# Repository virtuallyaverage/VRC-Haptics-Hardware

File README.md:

# Development moved to: https://github.com/VRC-Haptics/VRCH-Hardware

Hardware implementation for vrc haptics project. See: Firmware: [VRC-Haptics-Firmware](https://github.com/virtuallyaverage/VRC-Haptics-Firmware), Server: [VRC-Haptics-Hardware](https://github.com/virtuallyaverage/VRC-Haptics-Host)

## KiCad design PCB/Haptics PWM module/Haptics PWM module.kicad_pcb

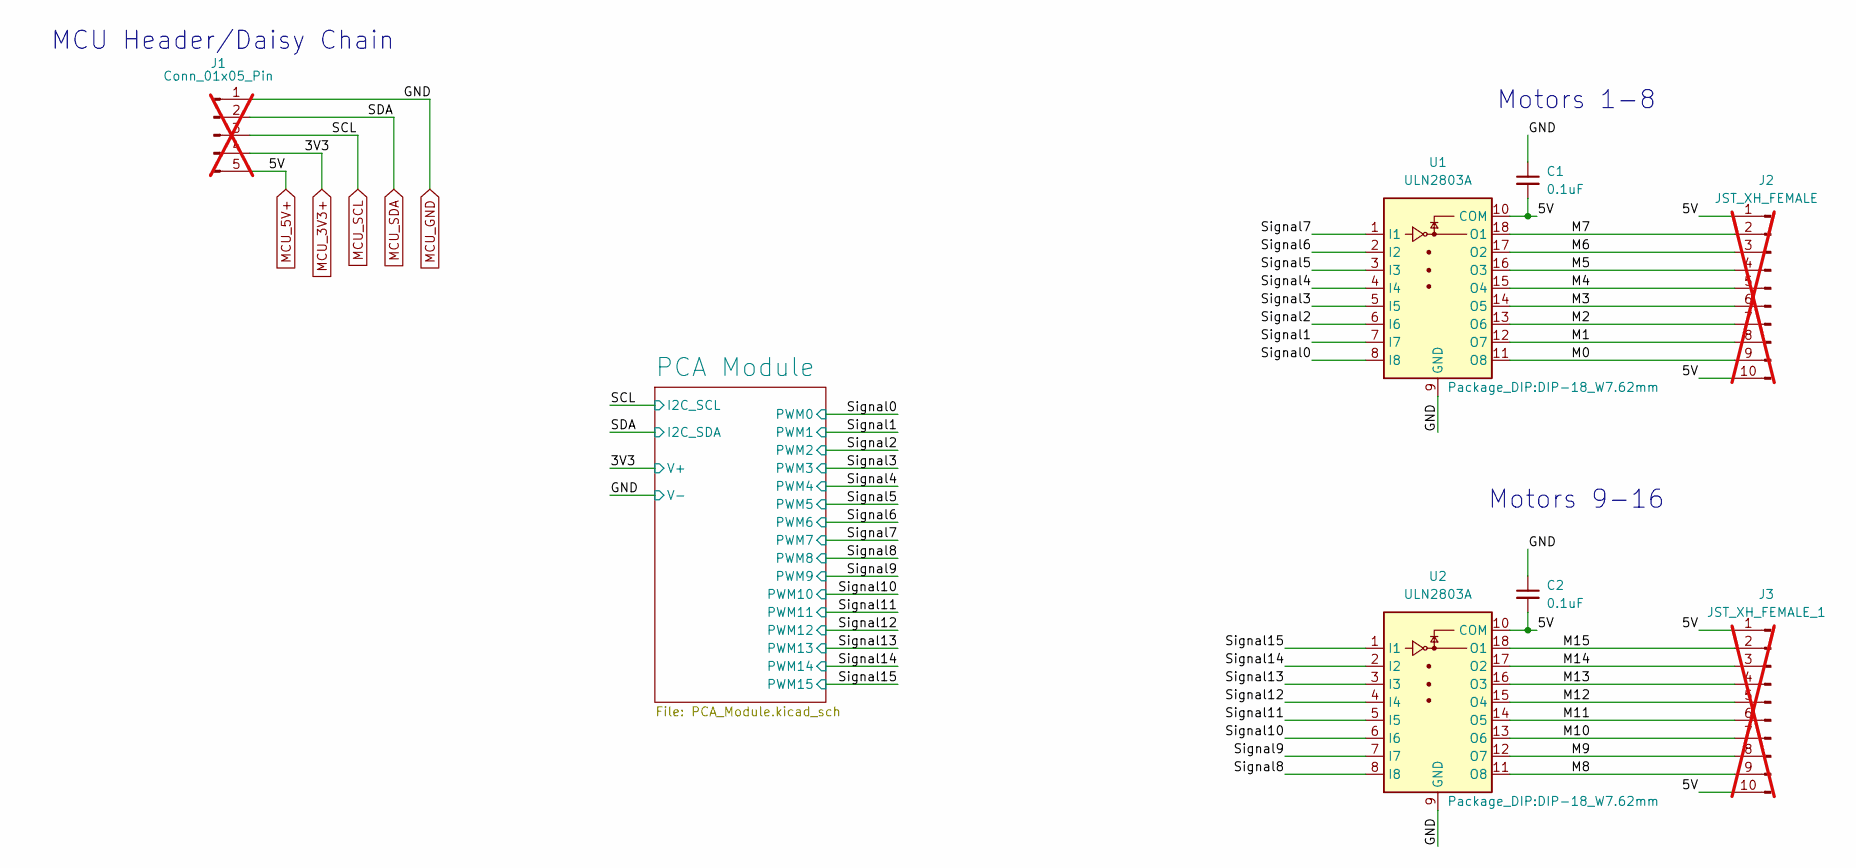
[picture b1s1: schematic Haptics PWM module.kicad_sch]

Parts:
C1, C2: 0.1uF; C_0805_2012Metric
J1: Conn_01x05_Pin; PinHeader_1x05_P2.54mm_Vertical; not fitted
J2: JST_XH_FEMALE; PinHeader_1x10_P2.00mm_Vertical; not fitted
J3: JST_XH_FEMALE_1; PinHeader_1x10_P2.00mm_Vertical; not fitted
U1, U2: ULN2803A; DIP-18_W7.62mm

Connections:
/M0: J2.9, U1.11 (O8)
/M1: J2.8, U1.12 (O7)
/M2: J2.7, U1.13 (O6)
/M3: J2.6, U1.14 (O5)
/M4: J2.5, U1.15 (O4)
/M5: J2.4, U1.16 (O3)
/M6: J2.3, U1.17 (O2)
/M7: J2.2, U1.18 (O1)
/M8: J3.9, U2.11 (O8)
/M9: J3.8, U2.12 (O7)
/M10: J3.7, U2.13 (O6)
/M11: J3.6, U2.14 (O5)
/M12: J3.5, U2.15 (O4)
/M13: J3.4, U2.16 (O3)
/M14: J3.3, U2.17 (O2)
/M15: J3.2, U2.18 (O1)
/Signal0: U1.8 (I8); also elsewhere on the board
/Signal1: U1.7 (I7); also elsewhere on the board
/Signal2: U1.6 (I6); also elsewhere on the board
/Signal3: U1.5 (I5); also elsewhere on the board
/Signal4: U1.4 (I4); also elsewhere on the board
/Signal5: U1.3 (I3); also elsewhere on the board
/Signal6: U1.2 (I2); also elsewhere on the board
/Signal7: U1.1 (I1); also elsewhere on the board
/Signal8: U2.8 (I8); also elsewhere on the board
/Signal9: U2.7 (I7); also elsewhere on the board
/Signal10: U2.6 (I6); also elsewhere on the board
/Signal11: U2.5 (I5); also elsewhere on the board
/Signal12: U2.4 (I4); also elsewhere on the board
/Signal13: U2.3 (I3); also elsewhere on the board
/Signal14: U2.2 (I2); also elsewhere on the board
/Signal15: U2.1 (I1); also elsewhere on the board
MCU_3V3+: J1.4; also elsewhere on the board
MCU_5V+: C1.2, C2.2, J1.5, J2.1, J2.10, J3.1, J3.10, U1.10 (COM), U2.10 (COM)
MCU_GND: C1.1, C2.1, J1.1, U1.9 (GND), U2.9 (GND); also elsewhere on the board
MCU_SCL: J1.3; also elsewhere on the board
MCU_SDA: J1.2; also elsewhere on the board

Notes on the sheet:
Motors 1-8
Motors 9-16
MCU Header/Daisy Chain

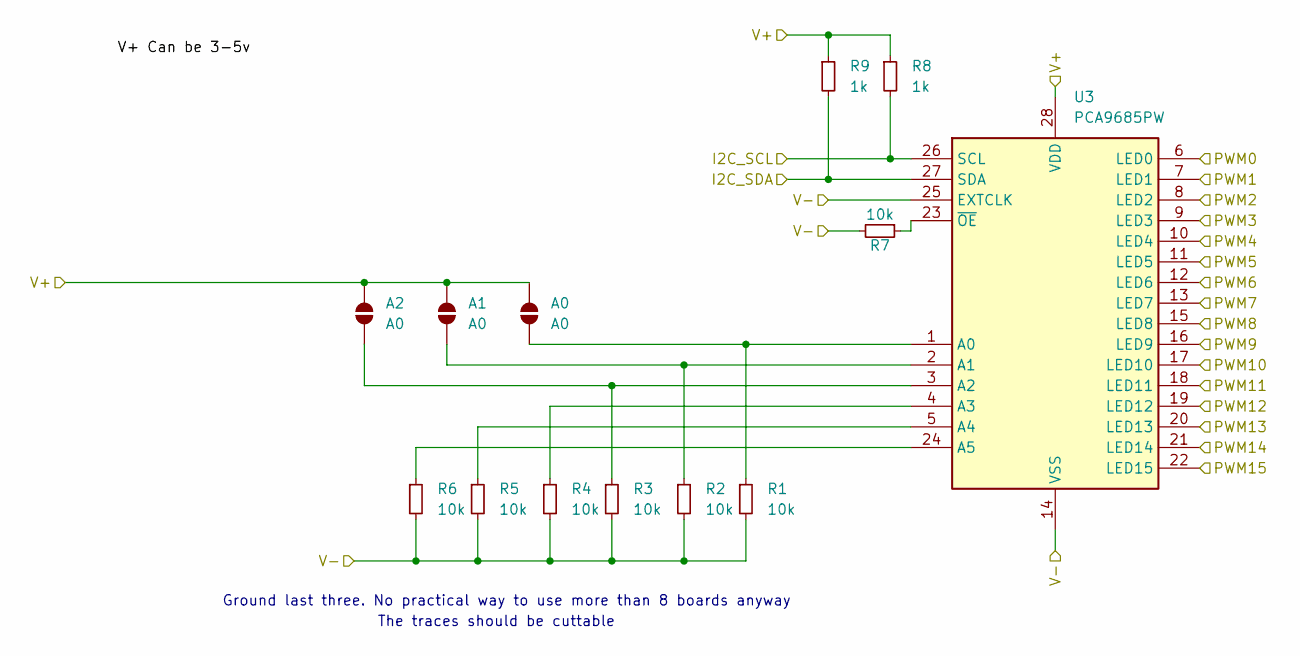
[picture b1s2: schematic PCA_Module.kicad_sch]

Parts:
A0, A1, A2: A0; SolderJumper-2_P1.3mm_Open_TrianglePad1.0x1.5mm
R1, R2, R3, R4, R5, R6, R7: 10k; R_0805_2012Metric
R8, R9: 1k; R_0805_2012Metric
U3: PCA9685PW; TSSOP-28_4.4x9.7mm_P0.65mm

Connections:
/Signal0: U3.6 (LED0); also elsewhere on the board
/Signal1: U3.7 (LED1); also elsewhere on the board
/Signal2: U3.8 (LED2); also elsewhere on the board
/Signal3: U3.9 (LED3); also elsewhere on the board
/Signal4: U3.10 (LED4); also elsewhere on the board
/Signal5: U3.11 (LED5); also elsewhere on the board
/Signal6: U3.12 (LED6); also elsewhere on the board
/Signal7: U3.13 (LED7); also elsewhere on the board
/Signal8: U3.15 (LED8); also elsewhere on the board
/Signal9: U3.16 (LED9); also elsewhere on the board
/Signal10: U3.17 (LED10); also elsewhere on the board
/Signal11: U3.18 (LED11); also elsewhere on the board
/Signal12: U3.19 (LED12); also elsewhere on the board
/Signal13: U3.20 (LED13); also elsewhere on the board
/Signal14: U3.21 (LED14); also elsewhere on the board
/Signal15: U3.22 (LED15); also elsewhere on the board
MCU_3V3+: A0.2 (B), A1.2 (B), A2.2 (B), R8.1, R9.1, U3.28 (VDD); also elsewhere on the board
MCU_GND: R1.2, R2.2, R3.2, R4.2, R5.2, R6.2, R7.2, U3.14 (VSS), U3.25 (EXTCLK); also elsewhere on the board
MCU_SCL: R8.2, U3.26 (SCL); also elsewhere on the board
MCU_SDA: R9.2, U3.27 (SDA); also elsewhere on the board
unnamed: A0.1 (A), R1.1, U3.1 (A0)
unnamed: A1.1 (A), R2.1, U3.2 (A1)
unnamed: A2.1 (A), R3.1, U3.3 (A2)
unnamed: R4.1, U3.4 (A3)
unnamed: R5.1, U3.5 (A4)
unnamed: R6.1, U3.24 (A5)
unnamed: R7.1, U3.23 (~OE)

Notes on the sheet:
The traces should be cuttable
Ground last three. No practical way to use more than 8 boards anyway

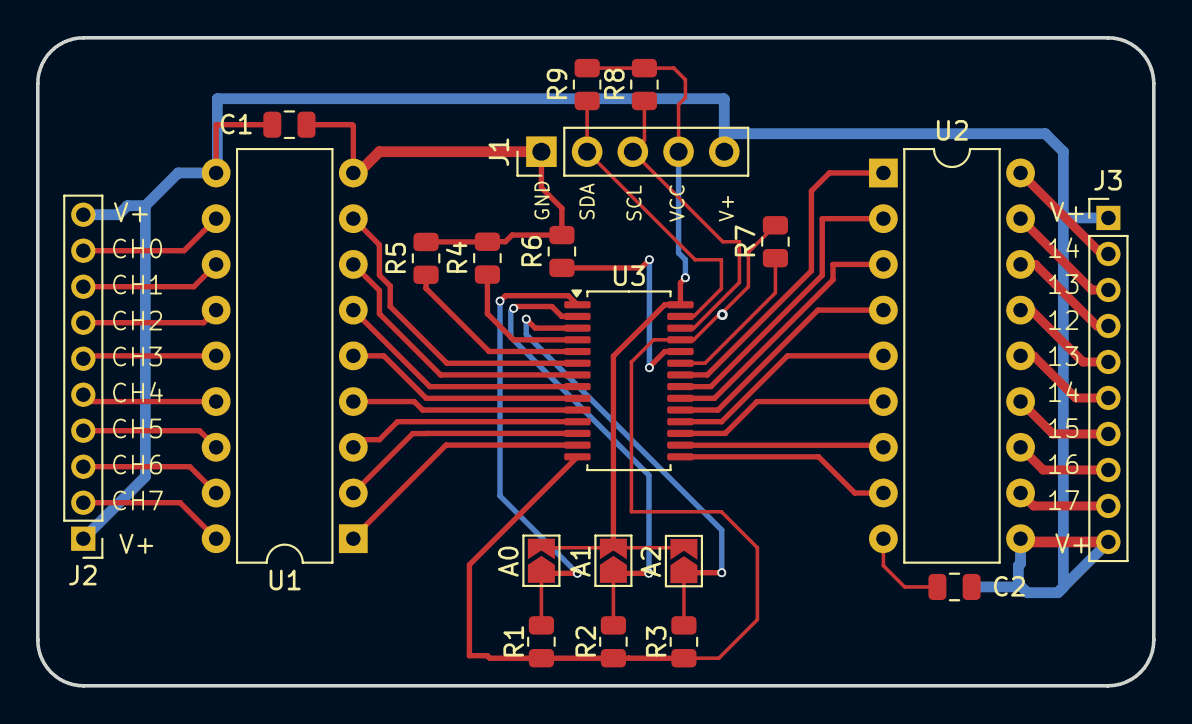
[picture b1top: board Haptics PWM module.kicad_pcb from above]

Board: 2 copper layers, 62.0 x 36.0 mm, 20 parts (0 on the bottom side), 44 nets.

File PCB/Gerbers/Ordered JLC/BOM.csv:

Comment,Designator,Footprint,JLCPCB Part#(optional)
1kΩ,"R9,R8",R_0805_2012Metric,C17513
10kΩ,"R5,R4,R7,R6,R2,R1,R3",R_0805_2012Metric,C17414
0.1uF,"C1,C2",C_0805_2012Metric,C49678
PCA9685PW,U3,TSSOP-28_4.4x9.7mm_P0.65mm,C92206

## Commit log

2024-09-12 Create README.md
    brief readme
2024-11-06 Added Ordered JLC version
2025-02-25 deprecation message
